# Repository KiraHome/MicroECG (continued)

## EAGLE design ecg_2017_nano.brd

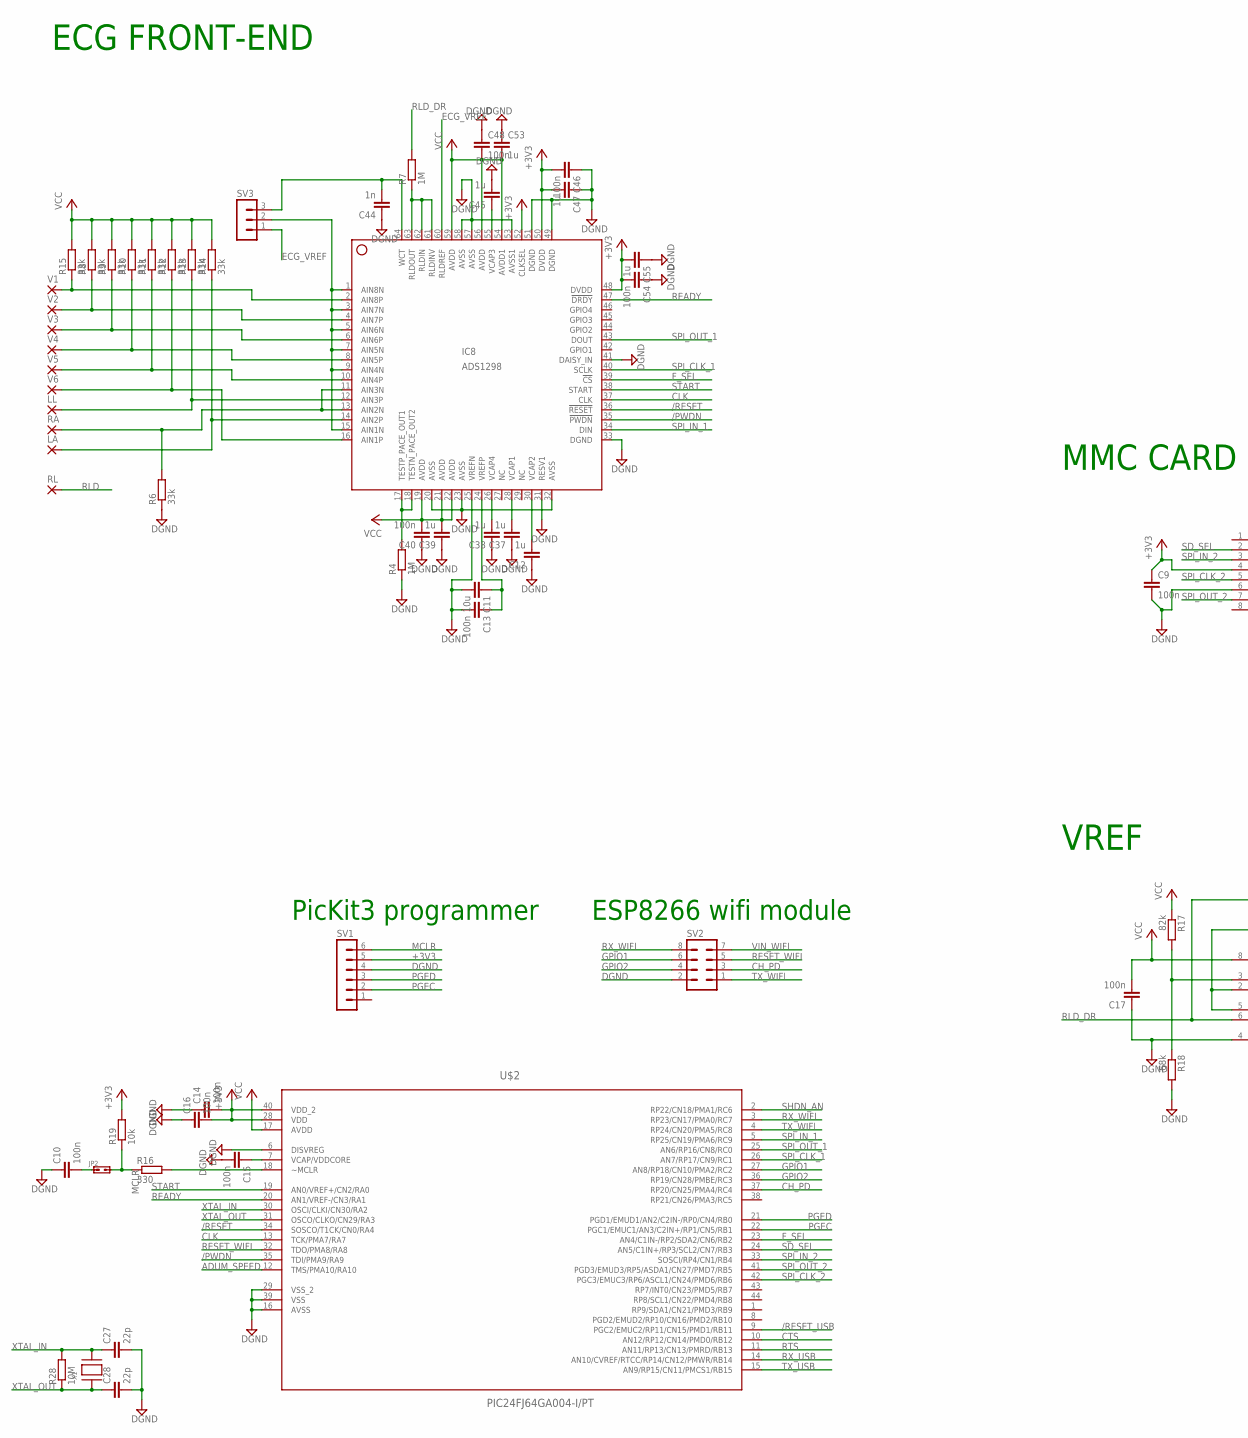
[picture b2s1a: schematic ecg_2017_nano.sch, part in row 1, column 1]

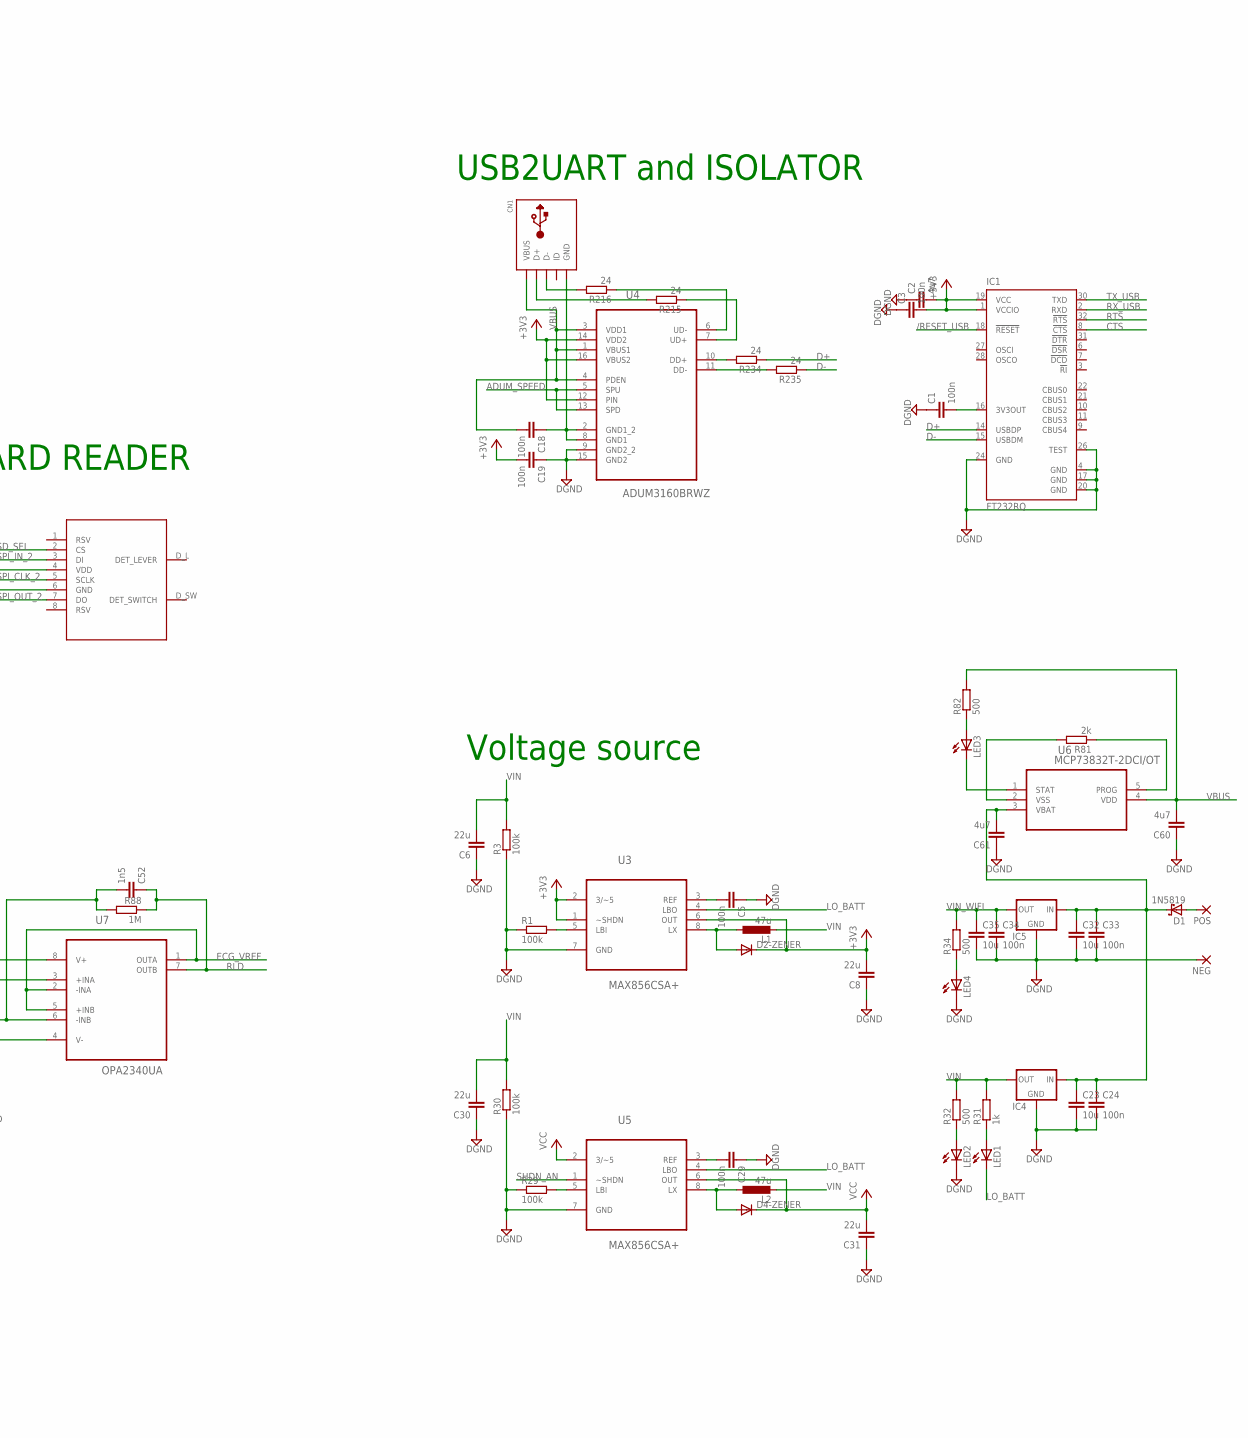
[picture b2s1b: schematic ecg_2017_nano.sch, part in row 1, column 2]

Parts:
C1, C3, C9, C10, C14, C15, C16, C17, C18, C19: 100n; C0603
C2: 4u7; C0603
C5, C24, C29, C33, C34: 100n; C0805
C6, C8, C30, C31: 22u; C0805
C11: 10u; C0402
C12, C37, C38, C39, C45, C47, C53, C55: 1u; C0402
C13, C40, C46, C48, C54: 100n; C0402
C23, C32, C35: 10u; C0805
C27, C28: 22p; C0603
C44: 1n; C0402
C52: 1n5; C0603
C60, C61: 4u7; C0805
CN1: USBMINIB; USB-MINIB
D1: 1N5819; DIODE_SMB
D2-ZENER, D4-ZENER: DIODE-MICROMELF-R; MICROMELF-R
IC1: FT232RQ; QFN32
IC4, IC5: R-783.3-0.5; R-78XX
IC8: ADS1298; HTQFP-64-PAP
JP2: JMP2; JP2
L1, L2: 47u; L2012C
LA: 2,54/1,0
LED1, LED2, LED3, LED4: LEDSML0805; SML0805
LL: 2,54/1,0
NEG: 2,54/1,0
POS: 2,54/1,0
R1, R3, R29, R30: 100k; R0805
R4, R7, R88: 1M; R0603
R6, R8, R9, R10, R11, R12, R13, R14, R15: 33k; R0603
R16: 330; R0603
R17: 82k; R0603
R18: 68k; R0603
R19: 10k; R0603
R28: 10M; R0603
R31: 1k; R0805
R32, R34, R82: 500; R0805
R81: 2k; R0805
R215, R216, R234, R235: 24; R0603
RA: 2,54/1,0
RL: 2,54/1,0
SV1: MA06-1
SV2: MA04-2
SV3: MA03-1
U3, U5: MAX856CSA+; SOIC127P600X175-8N
U4: ADUM3160BRWZ; SOIC127P1032X265-16N
U6: MCP73832T-2DCI/OT; SOT95P300X145-5N
U7: OPA2340UA; SOIC127P600X175-8N
U$1: MICROSDCARD_CONNECTOR
U$2: PIC24FJ64GA004-I/PT; QFP80P1200X1200X120-44N
V1, V2, V3, V4, V5, V6: 2,54/1,0
X1: XTAL-3.2X1.5; XTAL3215

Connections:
+3V3: C2.2, C3.2, C8.2, C9.1, C14.2, C16.2, C19.2, C46.2, C47.2, C54.2, C55.2, D2-ZENER.C, IC1.1 (VCCIO), IC1.19 (VCC), IC8.48 (DVDD), IC8.50 (DVDD), IC8.52 (CLKSEL), R19.2, SV1.5, U3.1 (~SHDN), U3.2 (3/~5), U3.6 (OUT), U4.12 (PIN), U4.14 (VDD2), U4.16 (VBUS2), U$1.4 (VDD), U$2.28 (VDD), U$2.40 (VDD_2)
/PWDN: IC8.35 (!PWDN), U$2.35 (TDI/PMA9/RA9)
/RESET: IC8.36 (!RESET), U$2.34 (SOSCO/T1CK/CN0/RA4)
/RESET_USB: IC1.18 (!RESET), U$2.9 (PGC2/EMUC2/RP11/CN15/PMD1/RB11)
ADUM_SPEED: U4.5 (SPU), U4.13 (SPD), U$2.12 (TMS/PMA10/RA10)
CH_PD: SV2.3, U$2.37 (RP20/CN25/PMA4/RC4)
CLK: IC8.37 (CLK), U$2.13 (TCK/PMA7/RA7)
CTS: IC1.8 (!CTS), U$2.10 (AN12/RP12/CN14/PMD0/RB12)
D+: IC1.14 (USBDP), R234.1
D-: IC1.15 (USBDM), R235.1
DGND: C1.1, C2.1, C3.1, C5.1, C6.1, C8.1, C9.2, C10.1, C11.2, C12.1, C13.2, C14.1, C15.2, C16.1, C17.1, C19.1, C23.2, C24.2, C27.2, C28.2, C29.1, C30.1, C31.1, C32.2, C33.2, C34.2, C35.2, C37.1, C38.1, C39.1, C40.1, C44.1, C45.2, C46.1, C47.1, C48.1, C53.1, C54.1, C55.1, C60.1, C61.1, IC1.4 (GND), IC1.17 (GND), IC1.20 (GND), IC1.24 (GND), IC1.26 (TEST), IC4.GND, IC5.GND, IC8.20 (AVSS), IC8.23 (AVSS), IC8.25 (VREFN), IC8.31 (RESV1), IC8.32 (AVSS), IC8.33 (DGND), IC8.41 (DAISY_IN), IC8.49 (DGND), IC8.51 (DGND), IC8.53 (AVSS1), IC8.57 (AVSS), IC8.58 (AVSS), LED2.C, LED4.C, NEG.1, R1.1, R3.1, R4.1, R6.1, R18.2, R29.1, R30.1, SV1.4, SV2.2, U3.7 (GND), U4.9 (GND2_2), U4.15 (GND2), U5.7 (GND), U7.4 (V-), U$1.6 (GND), U$2.6 (DISVREG), U$2.16 (AVSS), U$2.29 (VSS_2), U$2.39 (VSS)
ECG: IC8.1 (AIN8N), IC8.3 (AIN7N), IC8.5 (AIN6N), IC8.7 (AIN5N), IC8.9 (AIN4N), IC8.15 (AIN1N), SV3.2
ECG_VREF: IC8.60 (RLDREF), SV3.1, U7.1 (OUTA), U7.2 (-INA), U7.5 (+INB)
F_SEL: IC8.39 (!CS), U$2.23 (AN4/C1IN-/RP2/SDA2/CN6/RB2)
GPIO1: SV2.6, U$2.27 (AN8/RP18/CN10/PMA2/RC2)
GPIO2: SV2.4, U$2.36 (RP19/CN28/PMBE/RC3)
LO_BATT: LED1.C, U3.4 (LBO), U5.4 (LBO)
MCLR: JP2.2, R16.1, R19.1, SV1.6
unnamed: C5.2, U3.3 (REF)
unnamed: R1.2, U3.5 (LBI)
unnamed: IC8.17 (TESTP_PACE_OUT1), IC8.18 (TESTN_PACE_OUT2), R4.2
unnamed: D2-ZENER.A, L1.1, U3.8 (LX)
unnamed: IC8.14 (AIN2P), LA.1, R14.1
unnamed: IC8.16 (AIN1P), R12.1, V6.1
unnamed: IC8.11 (AIN3N), IC8.13 (AIN2N), R6.2, RA.1
unnamed: C12.2, IC8.30 (VCAP2)
unnamed: IC8.12 (AIN3P), LL.1, R13.1
unnamed: C1.2, IC1.16 (3V3OUT)
unnamed: IC8.10 (AIN4P), R11.1, V5.1
unnamed: D1.A (C), POS.1
unnamed: IC8.8 (AIN5P), R10.1, V4.1
unnamed: C11.1, C13.1, IC8.24 (VREFP)
unnamed: IC8.6 (AIN6P), R9.1, V3.1
unnamed: IC8.4 (AIN7P), R8.1, V2.1
unnamed: R17.2, R18.1, U7.3 (+INA)
unnamed: IC8.2 (AIN8P), R15.1, V1.1
unnamed: IC8.61 (RLDINV), IC8.62 (RLDIN), IC8.63 (RLDOUT), R7.1
unnamed: C10.2, JP2.1
unnamed: C29.2, U5.3 (REF)
unnamed: R16.2, U$2.18 (~MCLR)
unnamed: C15.1, U$2.7 (VCAP/VDDCORE)
unnamed: C23.1, C24.1, C32.1, C33.1, C61.2, D1.C (A), IC4.IN, IC5.IN, U6.3 (VBAT)
unnamed: R81.1, U6.5 (PROG)
unnamed: R81.2, U6.2 (VSS)
unnamed: LED3.A, R82.1
unnamed: LED3.C, U6.1 (STAT)
unnamed: C37.2, IC8.28 (VCAP1)
unnamed: C38.2, IC8.26 (VCAP4)
unnamed: R29.2, U5.5 (LBI)
unnamed: D4-ZENER.A, L2.1, U5.8 (LX)
unnamed: LED1.A, R31.1
unnamed: LED2.A, R32.1
unnamed: C44.2, IC8.64 (WCT), SV3.3
unnamed: LED4.A, R34.1
unnamed: C45.1, IC8.55 (VCAP3)
unnamed: R216.1, U4.6 (UD-)
unnamed: R215.1, U4.7 (UD+)
unnamed: CN1.D-, R216.2
unnamed: R234.2, U4.10 (DD+)
unnamed: CN1.D+, R215.2
unnamed: R235.2, U4.11 (DD-)
PGEC: SV1.2, U$2.22 (PGC1/EMUC1/AN3/C2IN+/RP1/CN5/RB1)
PGED: SV1.3, U$2.21 (PGD1/EMUD1/AN2/C2IN-/RP0/CN4/RB0)
READY: IC8.47 (!DRDY), U$2.20 (AN1/VREF-/CN3/RA1)
RESET_WIFI: SV2.5, U$2.32 (TDO/PMA8/RA8)
RLD: C52.1, R88.1, RL.1, U7.7 (OUTB)
RLD_DR: C52.2, R7.2, R88.2, U7.6 (-INB)
RTS: IC1.32 (!RTS), U$2.11 (AN11/RP13/CN13/PMRD/RB13)
RX_USB: IC1.2 (RXD), U$2.14 (AN10/CVREF/RTCC/RP14/CN12/PMWR/RB14)
RX_WIFI: SV2.8, U$2.3 (RP23/CN17/PMA0/RC7)
SD_SEL: U$1.2 (CS), U$2.24 (AN5/C1IN+/RP3/SCL2/CN7/RB3)
SHDN_AN: U5.1 (~SHDN), U$2.2 (RP22/CN18/PMA1/RC6)
SPI_CLK_1: IC8.40 (SCLK), U$2.26 (AN7/RP17/CN9/RC1)
SPI_CLK_2: U$1.5 (SCLK), U$2.42 (PGC3/EMUC3/RP6/ASCL1/CN24/PMD6/RB6)
SPI_IN_1: IC8.34 (DIN), U$2.5 (RP25/CN19/PMA6/RC9)
SPI_IN_2: U$1.3 (DI), U$2.33 (SOSCI/RP4/CN1/RB4)
SPI_OUT_1: IC8.43 (DOUT), U$2.25 (AN6/RP16/CN8/RC0)
SPI_OUT_2: U$1.7 (DO), U$2.41 (PGD3/EMUD3/RP5/ASDA1/CN27/PMD7/RB5)
START: IC8.38 (START), U$2.19 (AN0/VREF+/CN2/RA0)
TX_USB: IC1.30 (TXD), U$2.15 (AN9/RP15/CN11/PMCS1/RB15)
TX_WIFI: SV2.1, U$2.4 (RP24/CN20/PMA5/RC8)
USB_GND: C18.1, CN1.GND, U4.2 (GND1_2), U4.8 (GND1)
VBUS: C18.2, C60.2, CN1.VBUS, R82.2, U4.1 (VBUS1), U4.3 (VDD1), U4.4 (PDEN), U6.4 (VDD)
VCC: C17.2, C31.2, C39.2, C40.2, C48.2, C53.2, D4-ZENER.C, IC8.19 (AVDD), IC8.21 (AVDD), IC8.22 (AVDD), IC8.54 (AVDD1), IC8.56 (AVDD), IC8.59 (AVDD), R8.2, R9.2, R10.2, R11.2, R12.2, R13.2, R14.2, R15.2, R17.1, U5.2 (3/~5), U5.6 (OUT), U7.8 (V+), U$2.17 (AVDD)
VIN: C6.2, C30.2, IC4.OUT, L1.2, L2.2, R3.2, R30.2, R31.2, R32.2
VIN_WIFI: C34.1, C35.1, IC5.OUT, R34.2, SV2.7
XTAL_IN: C27.1, R28.2, U$2.30 (OSCI/CLKI/CN30/RA2), X1.P$2
XTAL_OUT: C28.1, R28.1, U$2.31 (OSCO/CLKO/CN29/RA3), X1.P$1

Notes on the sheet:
PicKit3 programmer
ESP8266 wifi module
Voltage source
USB2UART and ISOLATOR
MMC CARD READER
VREF
ECG FRONT-END

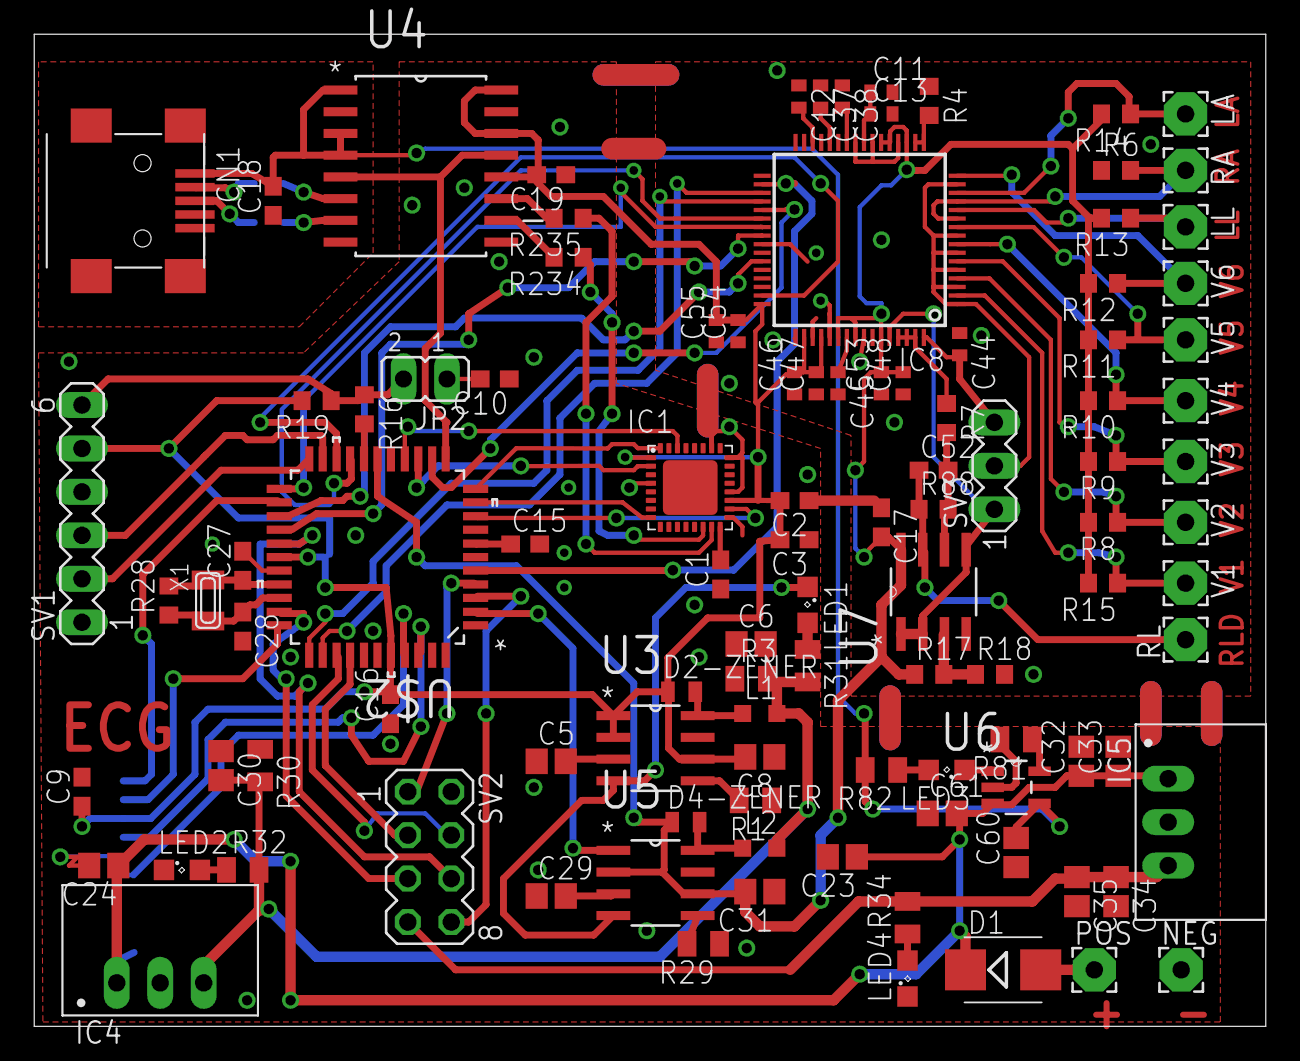
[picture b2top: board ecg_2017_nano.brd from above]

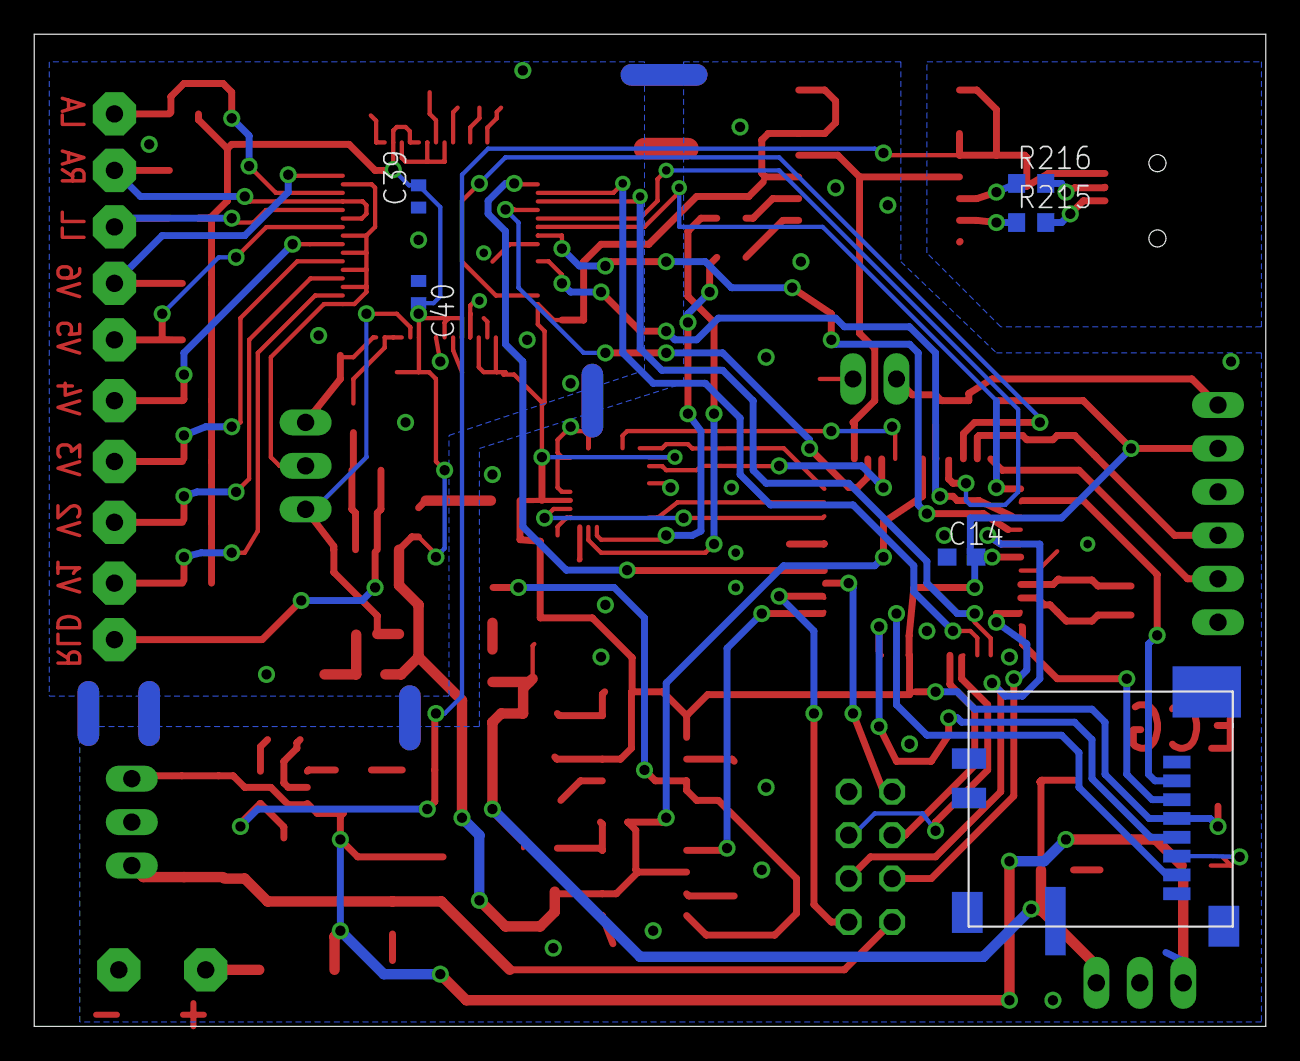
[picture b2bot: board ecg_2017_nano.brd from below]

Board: 2 copper layers, 72.0 x 58.0 mm, 111 parts (6 on the bottom side), 88 nets.

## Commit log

2018-12-12 ECG init commit
2022-01-11 Remove E01
